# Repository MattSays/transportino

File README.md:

# transportino

## Overview

## About the project

Transportino is an automated robot that can bring you things around the house using just your vocal assistant.

Making and also understanding this project will hopefully help enthusiasts that want to know more about robotics and automated navigation, learn the basics of it.

However, this project was born because of my curiosity to learn robotics so It is far from industrial perfection. If you have new ideas or you want to change something just make a pull request!

## Why this name?

Its name is literally made of two words: Transport and Arduino. 

## What's the main idea behind it?

This robot was originally meant to be a new version of an older one called [ArduCar](https://github.com/mattsays/arducar).

However it ended up being an entirely new robot that required me to make things entirely different and it was also an opportunity for me to learn more stuff about robotics, electronics, programming and also a little bit of mechanics.

This is just a project that I made to explore a field that was quite unknown to me and that made really passionate about.

So the main idea behind the whole project is making a robot which can move objects from one room of your house to another one.
The robot should know how to navigate in your house and at least bring objects at the entrance of the room.

## Known Limitations

Transportino has a raspberry pi 3 at its core, so by actually making It, I have encountered several performance issues that made me voluntarily limit the wanted capabilities of the robot.
For example, I had to separate the route planning algorithm from the actual robot and make it run on my local computer so I could lower the load on the raspberry.
It also would have been great if I implemented a more efficient cooling system.
Besides these major issues, I can proudly say that making this robot has made me learn a lot about what challenges are encountered when making a robot and I love it.

## What is it made of?

Transportino is composed by three important parts:
- [Mechanics](https://github.com/mattsays/transportino/tree/main/mechanics), the main structure, the usage of the right motors for a specific torque, etc.
- [Electronics](https://github.com/mattsays/transportino/tree/main/electronics), the main motherboard, data connections with raspberry pi and power management.
- [Software](https://github.com/mattsays/transportino/tree/main/code), the ros2 application that controls all the motors and analyzes data appropriately.

## To Do list

- [X] Make the main motherboard
- [X] Code the embedded part
- [X] Add ROS2 integration
- [X] Make a decent design that so Transportino looks sexy.
- [ ] Add integration with Amazon Alexa.
- [ ] Add a speaker so Transportino can also talk.
- [X] Add some cool aesthetics.

## Some cool renderings and animations 

## What is that 46 logo?

This logo it literally has no sense, it is from a startup idea named "Fortisix" that I had some time ago which had this beautiful and simple logo.

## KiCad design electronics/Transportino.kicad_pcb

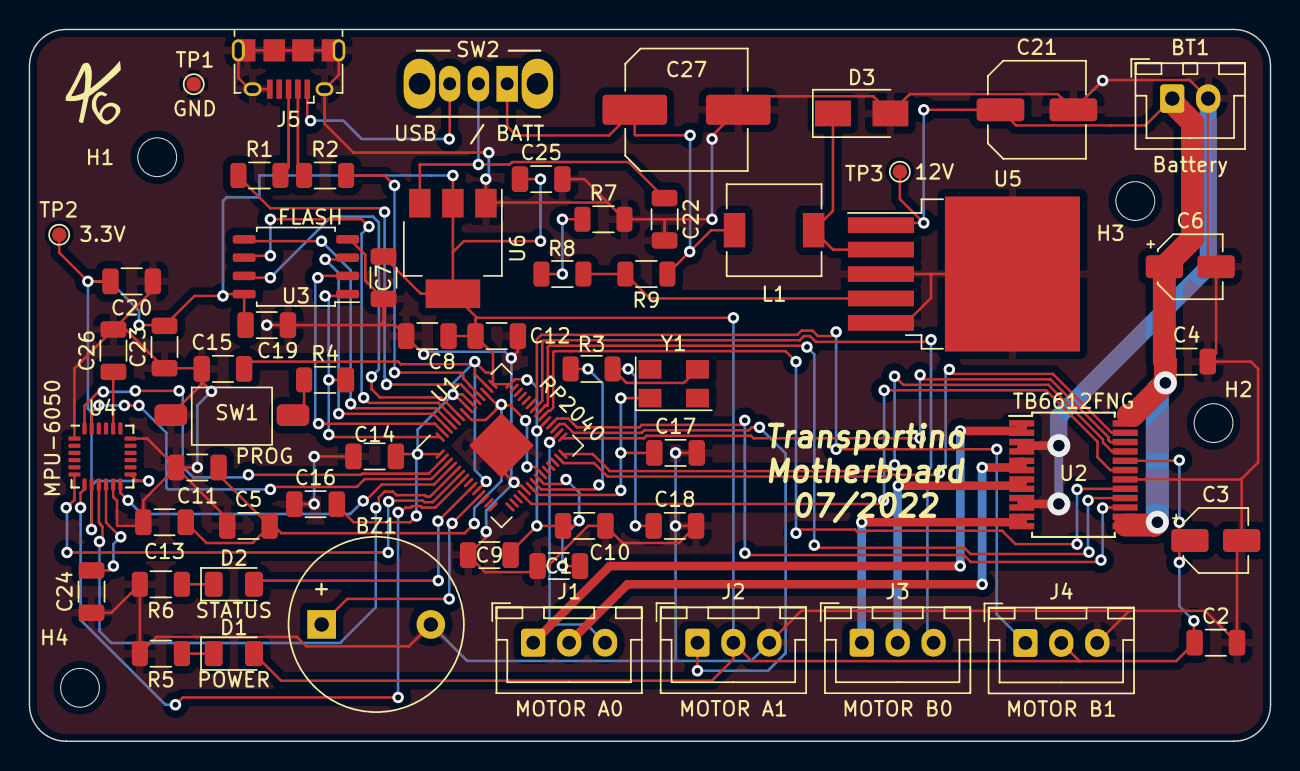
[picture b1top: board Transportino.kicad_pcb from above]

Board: 2 copper layers, 86.4 x 49.5 mm, 63 parts (0 on the bottom side), 51 nets.

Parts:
BT1: Battery; JST_XH_B2B-XH-A_1x02_P2.50mm_Vertical
BZ1: BUZZ; Buzzer_12x9.5RM7.6
C1, C2, C4, C5, C7, C8, C9, C10, C11, C12, C14, C16, C23, C24: 0.1u; C_1206_3216Metric
C3, C6: 10u; CP_Elec_4x5.4
C13, C15: 1u; C_1206_3216Metric
C17, C18: 27p; C_1206_3216Metric
C19, C22, C25: 10u; C_1206_3216Metric
C20: 10n; C_1206_3216Metric
C21: 68u; C_Elec_6.3x5.4
C26: 2.2n; C_1206_3216Metric
C27: 330u; C_Elec_8x10.2
D1: POWER; LED_1206_3216Metric
D2: STATUS; LED_1206_3216Metric
D3: SS32; D_SMA
H1, H2, H3, H4: MountingHole; MountingHole_2.7mm_M2.5
J1: MOTOR A0; JST_XH_B3B-XH-A_1x03_P2.50mm_Vertical
J2: MOTOR A1; JST_XH_B3B-XH-A_1x03_P2.50mm_Vertical
J3: MOTOR B0; JST_XH_B3B-XH-A_1x03_P2.50mm_Vertical
J4: MOTOR B1; JST_XH_B3B-XH-A_1x03_P2.50mm_Vertical
J5: USB_B_Micro; USB_Micro-B_Amphenol_10118194_Horizontal
L1: 330uH; L_6.3x6.3_H3
R1, R2: 27.4; R_1206_3216Metric
R3, R4, R5, R6, R7, R8: 1k; R_1206_3216Metric
R9: 6.2k; R_1206_3216Metric
SW1: PROG; Button_SWITCH_6.1x3.7
SW2: SW_DPDT_x2; SW_CuK_OS102011MA1QN1_SPDT_Angled
TP1: TestPoint; TestPoint_Pad_D1.0mm
TP2: 3.3V; TestPoint_Pad_D1.0mm
TP3: 12V; TestPoint_Pad_D1.0mm
U1: RP2040; QFN-56_EP_7.75x7.75_Pitch0.4mm
U2: TB6612FNG; SSOP-24_5.3x8.2mm_P0.65mm
U3: FLASH; SOIC-8_5.23x5.23mm_P1.27mm
U4: MPU-6050; InvenSense_QFN-24_4x4mm_P0.5mm
U5: LM2575BU-ADJ; TO-263-5_TabPin3
U6: NCP1117-3.3_SOT223; SOT-223-3_TabPin2
Y1: 12Mhz; Crystal_SMD_5032-4Pin_5.0x3.2mm

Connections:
+1V1: C5.2, C11.2, C13.2, U1.23 (DVDD), U1.45 (VREG_VOUT), U1.50 (DVDD)
+3V3: C1.2, C2.1, C3.1, C7.2, C8.2, C9.2, C10.2, C12.2, C14.2, C15.2, C16.2, C19.1, C20.2, C23.2, C25.1, D1.2 (A), J2.2, J4.2, TP2.1, U1.1 (IOVDD), U1.10 (IOVDD), U1.22 (IOVDD), U1.33 (IOVDD), U1.42 (IOVDD), U1.43 (ADC_AVDD), U1.44 (VREG_VIN), U1.48 (USB_VDD), U1.49 (IOVDD), U2.20 (VCC), U3.8 (VCC), U4.8 (VDDIO), U4.13 (VDD), U6.2 (VO)
+5V: C22.1, SW2.2 (B), U6.3 (VI)
+12V: BT1.1 (+), C4.1, C6.1, C21.1, TP3.1, U2.13 (VM2), U2.14 (VM3), U2.24 (VM1), U5.1 (VIN)
/OUT: D3.1, L1.1, U5.2 (OUT)
/PROG_BTN: R4.1, SW1.2
AD0: U1.5 (GPIO3), U4.9 (AD0)
BUCK_CONVERTER: C27.1, L1.2, R9.1, SW2.1 (A)
BUZZ: BZ1.1 (-), U1.11 (GPIO8)
CtrlA0: U1.28 (GPIO17), U2.21 (AIN1)
CtrlA1: U1.29 (GPIO18), U2.22 (AIN2)
CtrlAPWM: U1.27 (GPIO16), U2.23 (PWMA)
CtrlB0: U1.34 (GPIO22), U2.17 (BIN1)
CtrlB1: U1.35 (GPIO23), U2.16 (BIN2)
CtrlBPWM: U1.32 (GPIO21), U2.15 (PWMB)
DRV_EN: U1.18 (GPIO15), U2.19 (STBY)
GND: BT1.2 (-), BZ1.2 (+), C1.1, C2.2, C3.2, C4.2, C5.1, C6.2, C7.1, C8.1, C9.1, C10.1, C11.1, C12.1, C13.1, C14.1, C15.1, C16.1, C17.2, C18.2, C19.2, C20.1, C21.2, C22.2, C23.1, C24.1, C25.2, C26.2, C27.2, D3.2, J2.3, J4.3, J5.5 (GND), J5.6 (Shield), R5.2, R6.2, R7.2, SW1.1, TP1.1, U1.19 (TESTEN), U1.57 (GND), U2.3 (PGND1), U2.4 (PGND1), U2.9 (PGND2), U2.10 (PGND2), U2.18 (GND), U3.4 (GND), U4.1 (CLKIN), U4.11 (FSYNC), U4.18 (GND), U5.3 (GND), U5.5 (~ON/OFF), U6.1 (GND)
INT: U1.4 (GPIO2), U4.12 (INT)
MotorA0: J1.1, U2.1 (AO1), U2.2 (AO1)
MotorA1: J1.2, U2.5 (AO2), U2.6 (AO2)
MotorAENC0: J1.3, U1.30 (GPIO19)
MotorAENC1: J2.1, U1.31 (GPIO20)
MotorB0: J3.1, U2.11 (BO1), U2.12 (BO1)
MotorB1: J3.2, U2.7 (BO2), U2.8 (BO2)
MotorBENC0: J3.3, U1.36 (GPIO24)
MotorBENC1: J4.1, U1.37 (GPIO25)
unnamed: C18.1, R3.1, Y1.3
unnamed: C24.2, U4.10 (REGOUT)
unnamed: C26.1, U4.20 (CPOUT)
unnamed: D1.1 (K), R5.1
unnamed: D2.1 (K), R6.1
unnamed: R1.1, U1.47 (USB_DP)
unnamed: R2.1, U1.46 (USB_DM)
unnamed: R7.1, R8.2
unnamed: R8.1, R9.2, U5.4 (FB)
QSPI_CSN: R4.2, U1.56 (QSPI_SS_N), U3.1 (~CS)
QSPI_SCLK: U1.52 (QSPI_SCLK), U3.6 (CLK)
QSPI_SD0: U1.53 (QSPI_SD0), U3.5 (DI(IO0))
QSPI_SD1: U1.55 (QSPI_SD1), U3.2 (DO(IO1))
QSPI_SD2: U1.54 (QSPI_SD2), U3.3 (IO2)
QSPI_SD3: U1.51 (QSPI_SD3), U3.7 (IO3)
SCL: U1.3 (GPIO1), U4.23 (SCL)
SDA: U1.2 (GPIO0), U4.24 (SDA)
STATUS_LED: D2.2 (A), U1.9 (GPIO7)
USB_D+: J5.3 (D+), R1.2
USB_D-: J5.2 (D-), R2.2
VBUS: J5.1 (VBUS), SW2.3 (C)
XCL: U1.7 (GPIO5), U4.7 (AUX_SCL)
XDA: U1.6 (GPIO4), U4.6 (AUX_SDA)
XIN: C17.1, U1.20 (XIN), Y1.1
XOUT: R3.2, U1.21 (XOUT)

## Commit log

2022-06-04 Removed MPU6050 symbol
2022-06-04 Rearranged components
2022-06-13 Changed components and added new ones
2022-06-14 Added some screenshots.
2022-06-15 Improved readme.md and added holes to mainboard
2022-06-16 Added link to the ArduCar repo
2022-06-16 Added more todos.
2022-06-21 Added mechanics part and some renderings.
2022-06-21 Adjusted images path
2022-06-21 Yet another path adjustment
2022-06-21 File name changed and added a new animation.
2022-06-21 Added markdown files
2022-07-09 Added ros part
2022-07-09 Fixed lines
2022-07-09 Removed code directory
2022-07-11 Added html bom
2022-07-11 Added html bom and modified gitignore
2022-07-12 Added more electronic documentation
2022-07-13 Changed wrong assigned crystal pin.
2022-07-16 Changed buzzer gpio pin.
2022-07-22 Added board firmware
2022-07-22 Removed cache folder
2022-07-24 Added project submodules
2022-07-24 Added submodule auto update system
2022-07-24 Auto updated submodule references
2022-08-08 Added urdf meshes and updated fusion file
2022-08-08 Set correct branches to git modules
2022-08-08 Fixed modules for the final time
2022-08-08 Removed transportino_urdf_meshes archive
2022-08-31 Added logo.
2022-09-24 Updated mechanics readme
2022-09-24 Modify mechanics markdown
